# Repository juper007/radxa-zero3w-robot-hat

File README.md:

# Radxa ZERO 3W Robot HAT

A **strict single-board port** of Pollen Robotics' Apache-2.0 [`elec_RPI_Robot_HAT`](https://github.com/pollen-robotics/elec_RPI_Robot_HAT) for the Radxa ZERO 3W.

## Scope

The active design preserves the upstream product architecture:

- one 65 × 31 mm four-layer HAT PCB;
- the upstream 5–28 V power-input and 5 V conversion concept;
- on-board Dynamixel TTL/RS-485 circuitry and connectors;
- on-board BMI088 IMU, audio codec, MEMS microphone, speaker and expansion connectors;
- the original routed PCB as the layout baseline.

There is **no power daughterboard** in this branch. The earlier split-power redesign is preserved separately on `archive/v027-split-hat` at commit `2f2afd8`.

## Radxa-specific changes

Only host-facing compatibility changes are active:

| Physical pins | Upstream use | Radxa ZERO 3W use |
|---|---|---|
| 3 / 5 | Raspberry Pi I2C1 (`GPIO2/3`) | RK3566 `I2C3_SDA/SCL_M0` |
| 8 / 10 | Raspberry Pi UART (`GPIO14/15`) | RK3566 `UART2_TX/RX_M0` |
| 12 / 35 / 38 / 40 | Raspberry Pi PCM/I2S | RK3566 `I2S3_SCLK/LRCK/SDI/SDO_M0` |
| 2 / 4 | 5 V host rail | Radxa 5 V input pins |
| 1 / 17 | 3.3 V | Radxa 3.3 V rail |

The schematic and PCB net names identify these Radxa functions instead of Raspberry Pi BCM names. The physical routes are retained because the required interfaces occupy the same header pins.

The Raspberry Pi HAT EEPROM is retained as upstream DNP. All four upstream Qwiic connectors are populated for functional parity. J5 remains on hardware I2C3 M0 pins 3/5 with the codec and IMU. J6/J7/J8 retain the upstream routed GPIO pairs and are exposed as independent open-drain `i2c-gpio` buses by [`software/overlays/radxa-zero3w-robot-hat-qwiic.dts`](software/overlays/radxa-zero3w-robot-hat-qwiic.dts). Their original 0 Ω links and 10 kΩ pull-ups are populated.

## Software requirement

Using hardware I2C3 M0 on pins 3/5 requires the Radxa device-tree configuration to select `i2c3m0_xfer`. On vendor device trees this can conflict with the FUSB302 USB-C PD controller on I2C3 M1; the software overlay and resulting USB-C behavior must be reviewed before release. The Qwiic parity overlay adds J6/J7/J8 as aliases `i2c10`, `i2c11` and `i2c12`; the intended OS image must enable `CONFIG_I2C_GPIO`, leave those six GPIOs unclaimed, and pass runtime enumeration and transfer tests.

## Source and validation

- Upstream source revision: `23eab11927f95ceca0dfa35bf182caeb7db39ea0`
- KiCad sources: [`hardware/kicad/`](hardware/kicad/)
- Change matrix: [`docs/09_STRICT_PORT_CHANGE_MATRIX.md`](docs/09_STRICT_PORT_CHANGE_MATRIX.md)
- Current status: [`docs/PROJECT_STATUS.md`](docs/PROJECT_STATUS.md)
- Power review: [`docs/10_POWER_INTEGRITY_REVIEW.md`](docs/10_POWER_INTEGRITY_REVIEW.md)
- Mechanical/RF review: [`docs/11_RADXA_MECHANICAL_REVIEW.md`](docs/11_RADXA_MECHANICAL_REVIEW.md)
- Validation evidence: [`validation/strict_port/`](validation/strict_port/)

The routed board is **not yet approved for fabrication**. KiCad 10.0.6 CI regenerates reports from both the port and pinned upstream commit and locks rule policy, J4, the C45/U9 power region and the filled zone. Current DRC has zero findings and zero unconnected items after project-local footprint vendoring. Remaining gates include J4 supplier/prototype signoff, C45 physical gap, the 2 A load/thermal envelope, single-source backfeed testing, external-antenna/OTA policy, cable access and final manufacturing-package review.

## License and attribution

The active KiCad design is a modified derivative of Pollen Robotics' `elec_RPI_Robot_HAT`, licensed under Apache License 2.0. Upstream authorship and the exact source revision are preserved in the project documentation.

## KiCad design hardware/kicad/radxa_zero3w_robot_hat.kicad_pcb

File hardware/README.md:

# Hardware

## Active strict-port design

The active KiCad project is a single-board derivative of Pollen Robotics' `elec_RPI_Robot_HAT` at upstream commit `23eab11927f95ceca0dfa35bf182caeb7db39ea0`.

- `kicad/radxa_zero3w_robot_hat.kicad_pro` — project
- `kicad/radxa_zero3w_robot_hat.kicad_sch` — top-level schematic
- `kicad/radxa_zero3w_robot_hat.kicad_pcb` — routed 65.00 × 30.90 mm Edge.Cuts-centerline PCB (approximately 65 × 31 mm)
- Fixed order stackup — 4-layer FR-4, 1.0 mm, 70/35/35/70 µm copper, ENIG
- `kicad/main.kicad_sch` — 40-pin header and board integration
- `kicad/power.kicad_sch` / `pwr_supply_charge.kicad_sch` — upstream single-board power concept with local C45 input-bypass correction
- `kicad/dynamixel.kicad_sch` — upstream TTL/RS-485 interface and connectors
- `kicad/sensors.kicad_sch` — upstream BMI088 and Qwiic circuitry
- `kicad/audio.kicad_sch` — upstream codec, microphone and speaker circuitry

There is no active power daughterboard. The earlier split design is isolated on `archive/v027-split-hat`.

## Applied host changes

Critical nets retain their upstream physical header pins and routed copper while using Radxa names:

- pins 3/5 — `I2C3_SDA_M0` / `I2C3_SCL_M0`
- pins 8/10 — `UART2_TX_M0` / `UART2_RX_M0`
- pins 12/35/38/40 — `I2S3_SCLK_M0` / `I2S3_LRCK_M0` / `I2S3_SDI_M0` / `I2S3_SDO_M0`

U4 remains DNP. J5/J6/J7/J8 are all populated to preserve the upstream Qwiic expansion function. J6 uses R18/R19 0 Ω links plus R20/R21 10 kΩ pull-ups; J7 uses R34/R35 pull-ups; J8 uses R38/R39 pull-ups. The preserved J6/J7/J8 GPIO pairs are configured as three independent software I2C buses by the Radxa overlay under `../software/overlays/`.

## Validation

See `../validation/strict_port/` and `kicad/check_strict_port.py`.

The adapted design has 48 ERC warnings: eight upstream footprint-link findings are resolved by the vendored project-local libraries, and one exact C45 `lib_symbol_mismatch` remains approved pending symbol-library cleanup. It retains 110 remaining `Datasheet` field parity warnings; one inherited J4 field mismatch was resolved by correcting the manufacturing identity. All 49 upstream DRC findings are resolved, so current native DRC contains zero findings and zero unconnected items. C45 adds 10 µF / 50 V X7R input bypass; C21/C22 metadata correctly states 22 µF / 10 V, and the local U9/D1/C22 routing plus filled zone are hash-locked. The current board has 128 footprints and 1,013 track/via items. Twelve exact footprint definitions and `fp-lib-table` are hash-locked by `vendored_footprints_manifest.json`. J4 vendor/prototype approval, C45's ≥4.0 mm PCB gap and ≥0.5 mm residual-clearance gate, the 2 A EVT load/thermal envelope, antenna policy and single-source power rule remain fabrication gates.

## Upstream libraries

The 12 footprint definitions needed for `Library_Pollen`, `LCSC_parts_lib` and the board-used `Package_TO_SOT_SMD` subset are vendored under `kicad/*.pretty/` and mapped by `kicad/fp-lib-table`. `kicad/vendored_footprints_manifest.json` pins the exact file inventory and hashes. This removes all native DRC footprint-library findings without changing the embedded PCB, placement, pads, nets or routing. Some 3D-model paths still retain upstream names for traceability and may require later model vendoring for complete assembly rendering.

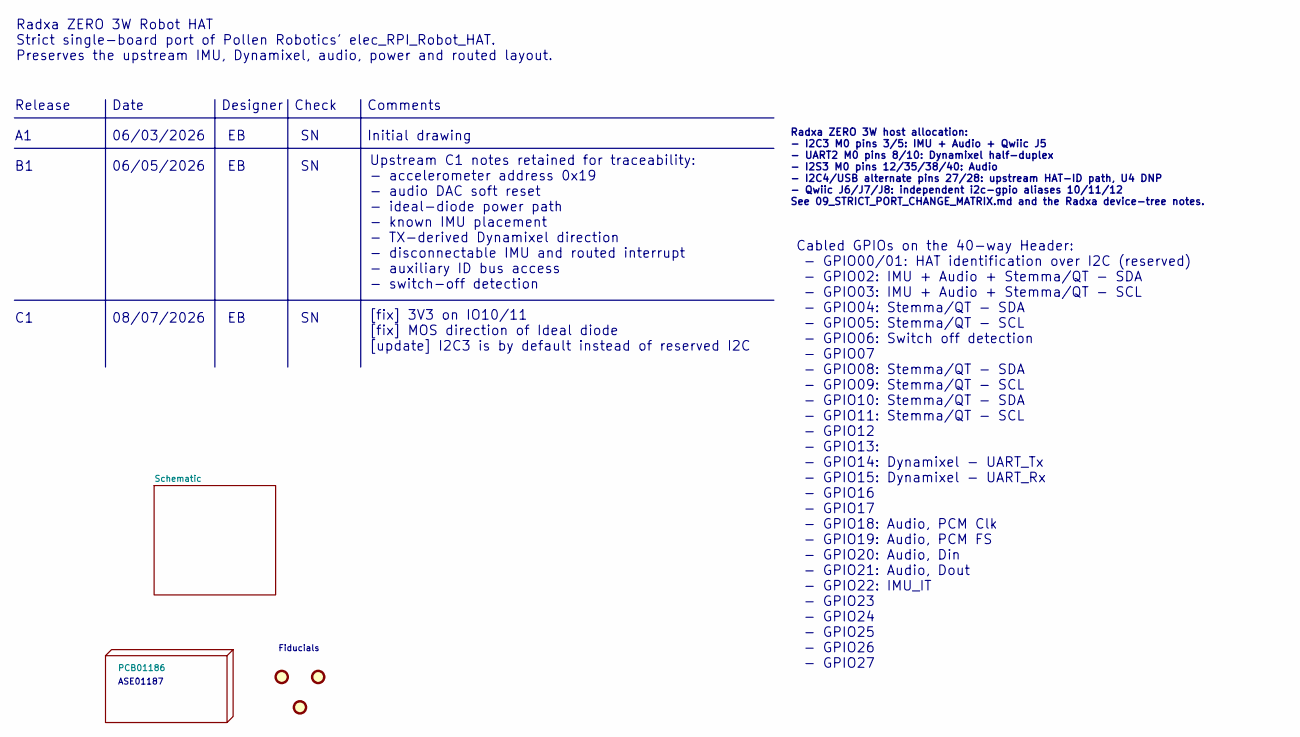
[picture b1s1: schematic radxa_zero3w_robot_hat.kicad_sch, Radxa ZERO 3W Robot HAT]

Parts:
FID1, FID2, FID3: DNP Fiducial; Fiducial_1mm_Mask2mm
H1: PCB01186

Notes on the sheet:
Upstream C1 notes retained for traceability: - accelerometer address 0x19 - audio DAC soft reset - ideal-diode power path - known IMU placement - TX-derived Dynamixel direction - disconnectable IMU and routed interrupt - auxiliary ID bus access - switch-off detection
Date
[fix] 3V3 on IO10/11 [fix] MOS direction of Ideal diode [update] I2C3 is by default instead of reserved I2C
Check
Release
Fiducials
Radxa ZERO 3W host allocation: - I2C3 M0 pins 3/5: IMU + Audio + Qwiic J5 - UART2 M0 pins 8/10: Dynamixel half-duplex - I2S3 M0 pins 12/35/38/40: Audio - I2C4/USB alternate pins 27/28: upstream HAT-ID path, U4 DNP - Qwiic J6/J7/J8: independent i2c-gpio aliases 10/11/12 See 09_STRICT_PORT_CHANGE_MAT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
08/07/2026
ASE01187
06/05/2026
Initial drawing
Radxa ZERO 3W Robot HAT Strict single-board port of Pollen Robotics' elec_RPI_Robot_HAT. Preserves the upstream IMU, Dynamixel, audio, power and routed layout.
Designer
Cabled GPIOs on the 40-way Header: - GPIO00/01: HAT identification over I2C (reserved) - GPIO02: IMU + Audio + Stemma/QT - SDA - GPIO03: IMU + Audio + Stemma/QT - SCL - GPIO04: Stemma/QT - SDA - GPIO05: Stemma/QT - SCL - GPIO06: Switch off detection - GPIO07 - GPIO08: Stemma/QT - SDA - GPIO09: Stem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
Comments
06/03/2026

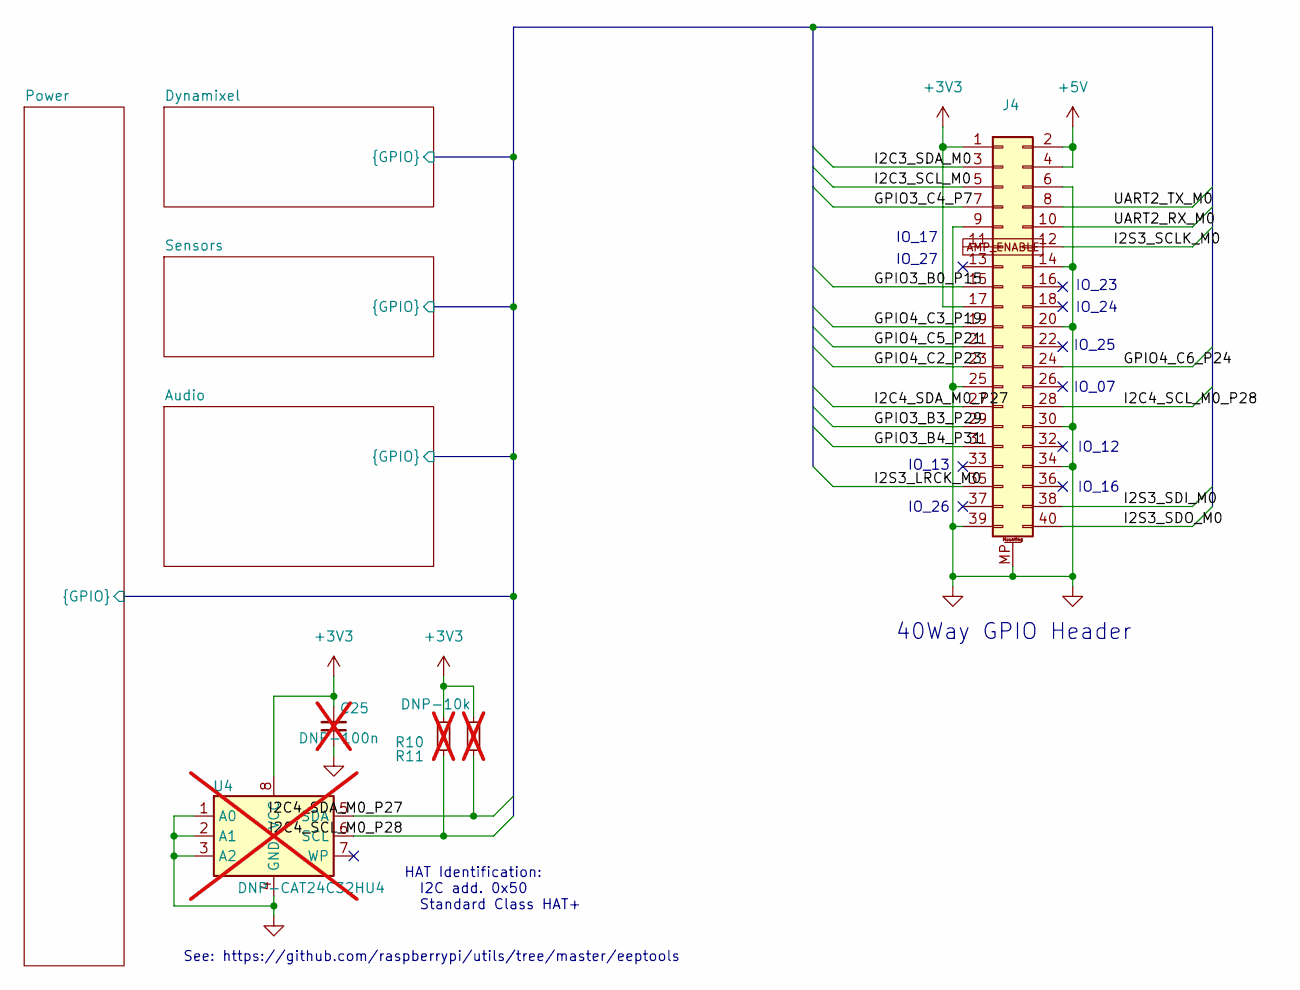
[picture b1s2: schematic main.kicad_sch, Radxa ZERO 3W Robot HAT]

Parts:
C25: DNP-100n; C_0402_1005Metric; not fitted
J4: Radxa ZERO 3W 2x20 HAT Header; PinHeader_2x20_P2.54mm_Vertical_with_rasp_HAT_zero_SMD_conn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; Part Description 2x20 2.54 mm surface-mount bottom-entry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
R10, R11: DNP-10k; R_0402_1005Metric; not fitted
U4: DNP-CAT24C32HU4; TDFN-8_L3.0-W2.0-P0.50-BL-EP; not fitted

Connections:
+3V3: C25.2, J4.1, J4.17, R10.1, R11.1, U4.8 (VCC); also elsewhere on the board
+5V: J4.2, J4.4; also elsewhere on the board
/Schematic/Audio/GPIO3_B0_P15: J4.15; also elsewhere on the board
/Schematic/Audio/GPIO3_B3_P29: J4.29; also elsewhere on the board
/Schematic/Audio/GPIO3_B4_P31: J4.31; also elsewhere on the board
/Schematic/Audio/GPIO3_C4_P7: J4.7; also elsewhere on the board
/Schematic/Audio/GPIO4_C2_P23: J4.23; also elsewhere on the board
/Schematic/Audio/GPIO4_C3_P19: J4.19; also elsewhere on the board
/Schematic/Audio/GPIO4_C5_P21: J4.21; also elsewhere on the board
/Schematic/Audio/GPIO4_C6_P24: J4.24; also elsewhere on the board
/Schematic/Audio/I2C3_SCL_M0: J4.5; also elsewhere on the board
/Schematic/Audio/I2C3_SDA_M0: J4.3; also elsewhere on the board
/Schematic/Audio/I2C4_SCL_M0_P28: J4.28, R10.2, U4.6 (SCL); also elsewhere on the board
/Schematic/Audio/I2C4_SDA_M0_P27: J4.27, R11.2, U4.5 (SDA); also elsewhere on the board
/Schematic/Audio/I2S3_LRCK_M0: J4.35; also elsewhere on the board
/Schematic/Audio/I2S3_SCLK_M0: J4.12; also elsewhere on the board
/Schematic/Audio/I2S3_SDI_M0: J4.38; also elsewhere on the board
/Schematic/Audio/I2S3_SDO_M0: J4.40; also elsewhere on the board
/Schematic/Audio/UART2_RX_M0: J4.10; also elsewhere on the board
/Schematic/Audio/UART2_TX_M0: J4.8; also elsewhere on the board
AMP_ENABLE: J4.11; also elsewhere on the board
GND: C25.1, J4.6, J4.9, J4.14, J4.20, J4.25, J4.30, J4.34, J4.39, J4.MP (MountPin), U4.1 (A0), U4.2 (A1), U4.3 (A2), U4.4 (GND); also elsewhere on the board

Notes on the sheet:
IO_07
IO_23
40Way GPIO Header
IO_13
IO_24
HAT Identification: I2C add. 0x50 Standard Class HAT+
IO_25
IO_17
IO_12
See: https://github.com/raspberrypi/utils/tree/master/eeptools
IO_16
IO_26
IO_27

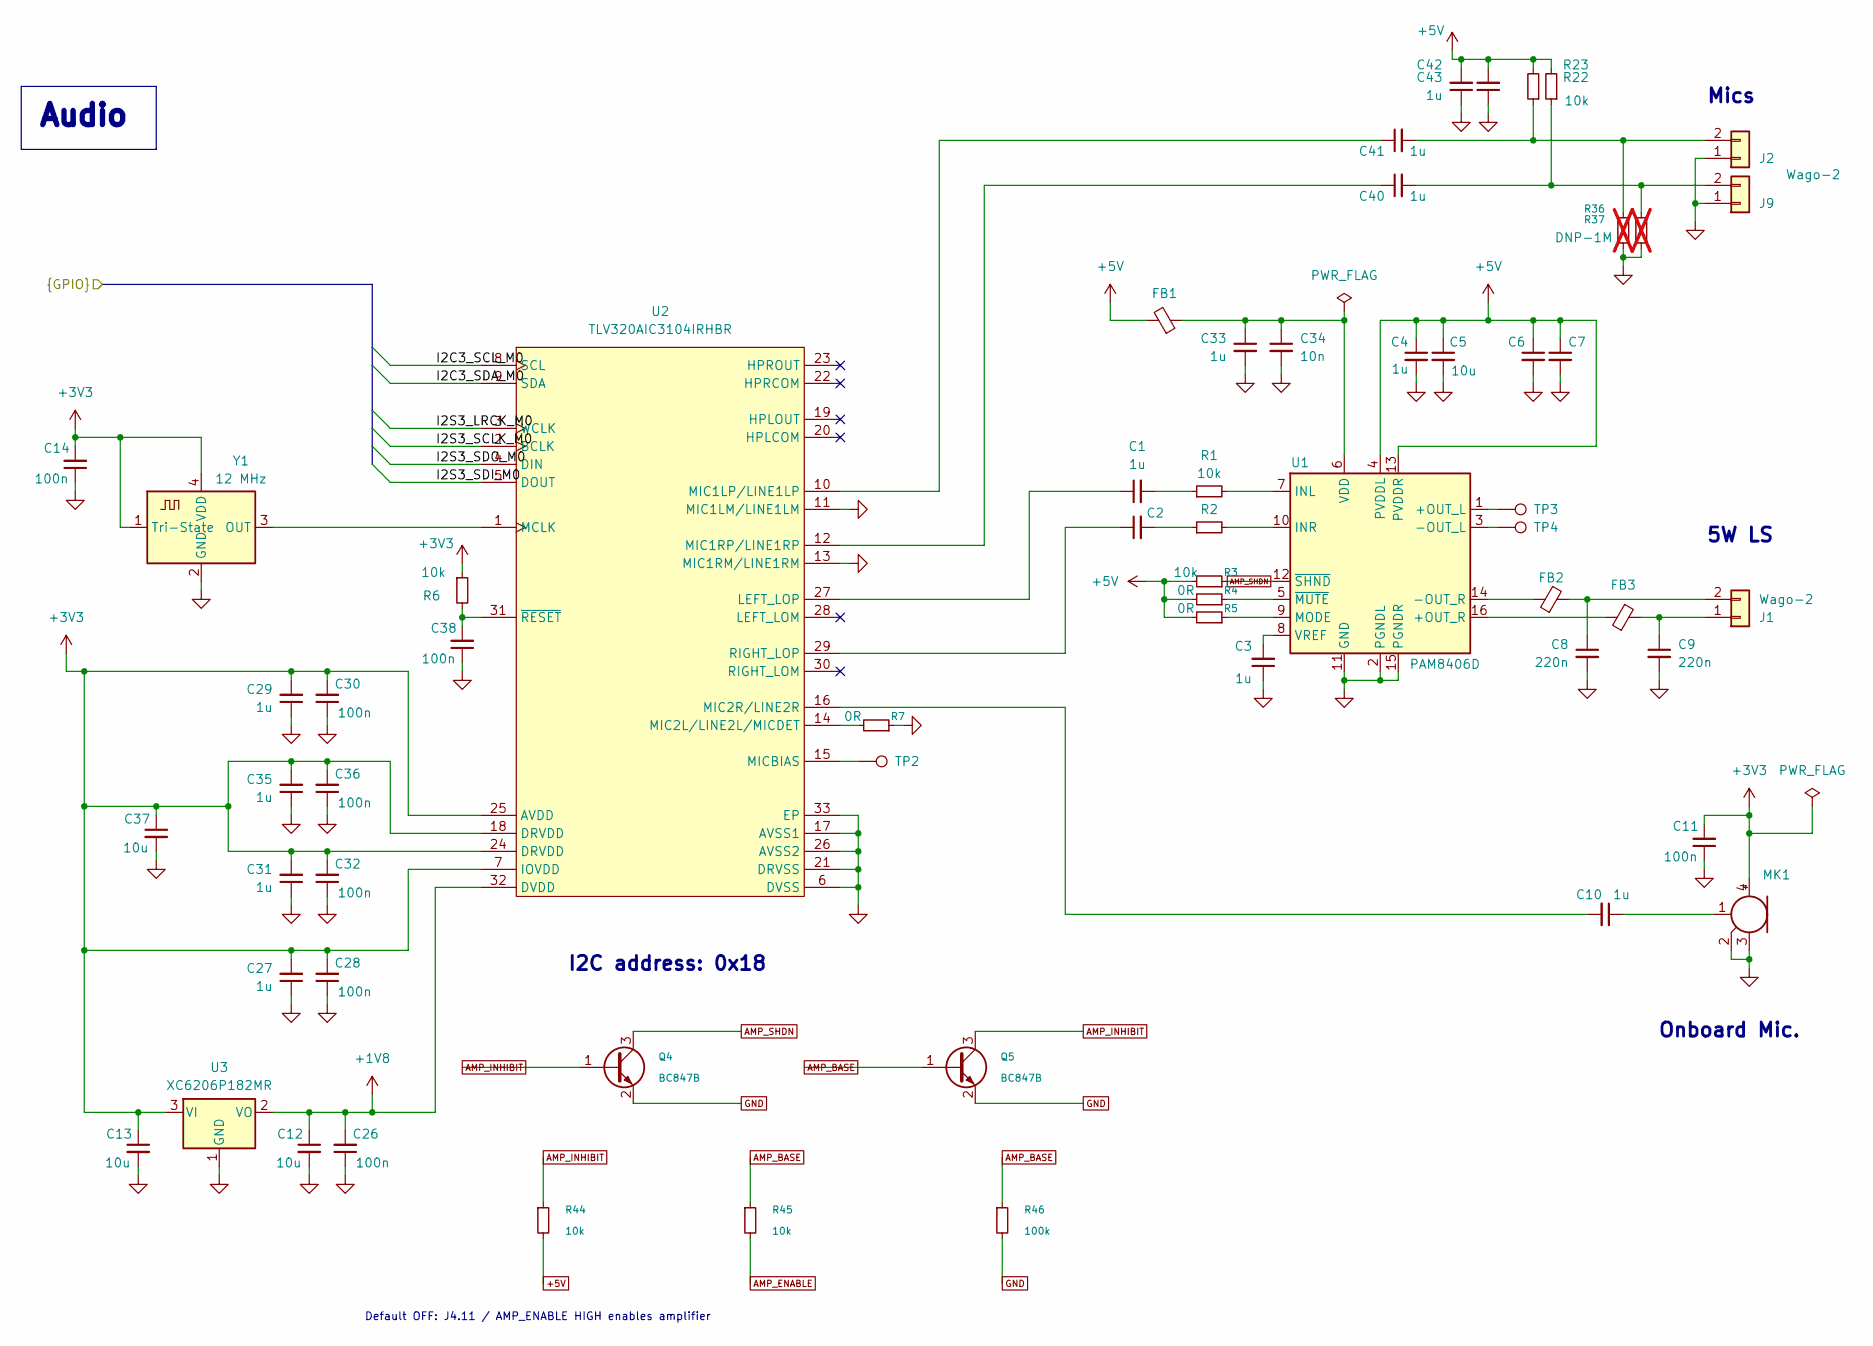
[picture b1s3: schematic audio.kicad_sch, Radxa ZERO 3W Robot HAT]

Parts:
C1, C2, C3, C4, C6, C10, C27, C29, C31, C33, C35, C40, C41, C42, C43: 1u; C_0402_1005Metric; LCSC Part C52923
C5, C7, C12, C13, C37: 10u; C_0603_1608Metric; LCSC Part C1691
C8, C9: 220n; C_0402_1005Metric; LCSC Part C71693
C11, C14, C26, C28, C30, C32, C36, C38: 100n; C_0402_1005Metric; LCSC Part C307331
C34: 10n; C_0402_1005Metric; LCSC Part C15195
FB1: 1.3A 600R@100MHz; L_0402_1005Metric; LCSC Part C76884
FB2, FB3: 2A - 120R@100MHz; L_0402_1005Metric; LCSC Part C88970
J1, J2, J9: Wago-2; Wago_2059-302_998-403; LCSC Part C2765060
MK1: Microphone_MEMS; MIC-SMD_4P-L2.8-W1.9-P1.84-TL; LCSC Part C7587901
Q4, Q5: BC847B; SOT-23; Manufacturer_Part_Number BC847B,215
R1, R2, R6, R22, R23: 10k; R_0402_1005Metric; LCSC Part C25744
R3, R44, R45: 10k; R_0402_1005Metric; Power Rating 0.063W; Tolerance 1%; Manufacturer_Part_Number RC0402FR-0710KL
R4, R5, R7: 0R; R_0402_1005Metric; LCSC Part C17168
R36, R37: DNP-1M; R_0402_1005Metric; LCSC Part C17168; not fitted
R46: 100k; R_0402_1005Metric; Power Rating 0.063W; Tolerance 1%; Manufacturer_Part_Number RC0402FR-07100KL
TP2, TP3, TP4: TestPoint; TestPoint_Loop_D2.50mm_Drill1.0mm_LowProfile
U1: PAM8406D; SOIC-16_3.9x9.9mm_P1.27mm; LCSC Part C86270
U2: TLV320AIC3104IRHBR; VQFN-32-1EP_5x5mm_P0.5mm_EP3.5x3.5mm; LCSC Part C181753
U3: XC6206P182MR; SOT-23-3; LCSC Part C347373
Y1: 12 MHz; Oscillator_SMD_Abracon_ASDMB-4Pin_2.5x2.0mm; LCSC Part C7425459

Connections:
+1V8: C12.1, C26.2, U2.32 (DVDD), U3.2 (VO)
+3V3: C11.2, C13.1, C14.2, C27.2, C28.2, C29.2, C30.2, C31.2, C32.2, C35.2, C36.2, C37.1, MK1.4 (+), R6.1, U2.7 (IOVDD), U2.18 (DRVDD), U2.24 (DRVDD), U2.25 (AVDD), U3.3 (VI), Y1.1 (Tri-State), Y1.4 (VDD); also elsewhere on the board
+5V: C4.1, C5.1, C6.1, C7.1, C42.2, C43.2, FB1.2, R3.2, R4.2, R5.2, R22.2, R23.2, R44.2, U1.4 (PVDDL), U1.13 (PVDDR); also elsewhere on the board
/Schematic/Audio/I2C3_SCL_M0: U2.8 (SCL); also elsewhere on the board
/Schematic/Audio/I2C3_SDA_M0: U2.9 (SDA); also elsewhere on the board
/Schematic/Audio/I2S3_LRCK_M0: U2.3 (WCLK); also elsewhere on the board
/Schematic/Audio/I2S3_SCLK_M0: U2.2 (BCLK); also elsewhere on the board
/Schematic/Audio/I2S3_SDI_M0: U2.5 (DOUT); also elsewhere on the board
/Schematic/Audio/I2S3_SDO_M0: U2.4 (DIN); also elsewhere on the board
AMP_BASE: Q5.1 (B), R45.1, R46.1
AMP_ENABLE: R45.2; also elsewhere on the board
AMP_INHIBIT: Q4.1 (B), Q5.3 (C), R44.1
AMP_SHDN: Q4.3 (C), R3.1, U1.12 (~SHND)
GND: C3.1, C4.2, C5.2, C6.2, C7.2, C8.2, C9.2, C11.1, C12.2, C13.2, C14.1, C26.1, C27.1, C28.1, C29.1, C30.1, C31.1, C32.1, C33.2, C34.2, C35.1, C36.1, C37.2, C38.1, C42.1, C43.1, J2.1, J9.1, MK1.2 (-), MK1.3 (-), Q4.2 (E), Q5.2 (E), R7.1, R36.1, R37.1, R46.2, U1.2 (PGNDL), U1.11 (GND), U1.15 (PGNDR), U2.6 (DVSS), U2.11 (MIC1LM/LINE1LM), U2.13 (MIC1RM/LINE1RM), U2.17 (AVSS1), U2.21 (DRVSS), U2.26 (AVSS2), U2.33 (EP), U3.1 (GND), Y1.2 (GND); also elsewhere on the board
unnamed: C1.2, R1.1
unnamed: C2.2, R2.1
unnamed: C10.1, MK1.1 (-)
unnamed: C9.1, FB3.2, J1.1
unnamed: C8.1, FB2.2, J1.2
unnamed: C41.2, J2.2, R22.1, R36.2
unnamed: C40.2, J9.2, R23.1, R37.2
unnamed: TP3.1, U1.1 (+OUT_L)
unnamed: FB3.1, U1.16 (+OUT_R)
unnamed: TP4.1, U1.3 (-OUT_L)
unnamed: FB2.1, U1.14 (-OUT_R)
unnamed: R1.2, U1.7 (INL)
unnamed: R2.2, U1.10 (INR)
unnamed: R5.1, U1.9 (MODE)
unnamed: C33.1, C34.1, FB1.1, U1.6 (VDD)
unnamed: C3.2, U1.8 (VREF)
unnamed: R4.1, U1.5 (~MUTE)
unnamed: C1.1, U2.27 (LEFT_LOP)
unnamed: U2.1 (MCLK), Y1.3 (OUT)
unnamed: C41.1, U2.10 (MIC1LP/LINE1LP)
unnamed: C40.1, U2.12 (MIC1RP/LINE1RP)
unnamed: R7.2, U2.14 (MIC2L/LINE2L/MICDET)
unnamed: C10.2, U2.16 (MIC2R/LINE2R)
unnamed: TP2.1, U2.15 (MICBIAS)
unnamed: C2.1, U2.29 (RIGHT_LOP)
unnamed: C38.2, R6.2, U2.31 (~RESET)

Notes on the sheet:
Onboard Mic.
5W LS
Mics
I2C address: 0x18
Audio
Default OFF: J4.11 / AMP_ENABLE HIGH enables amplifier

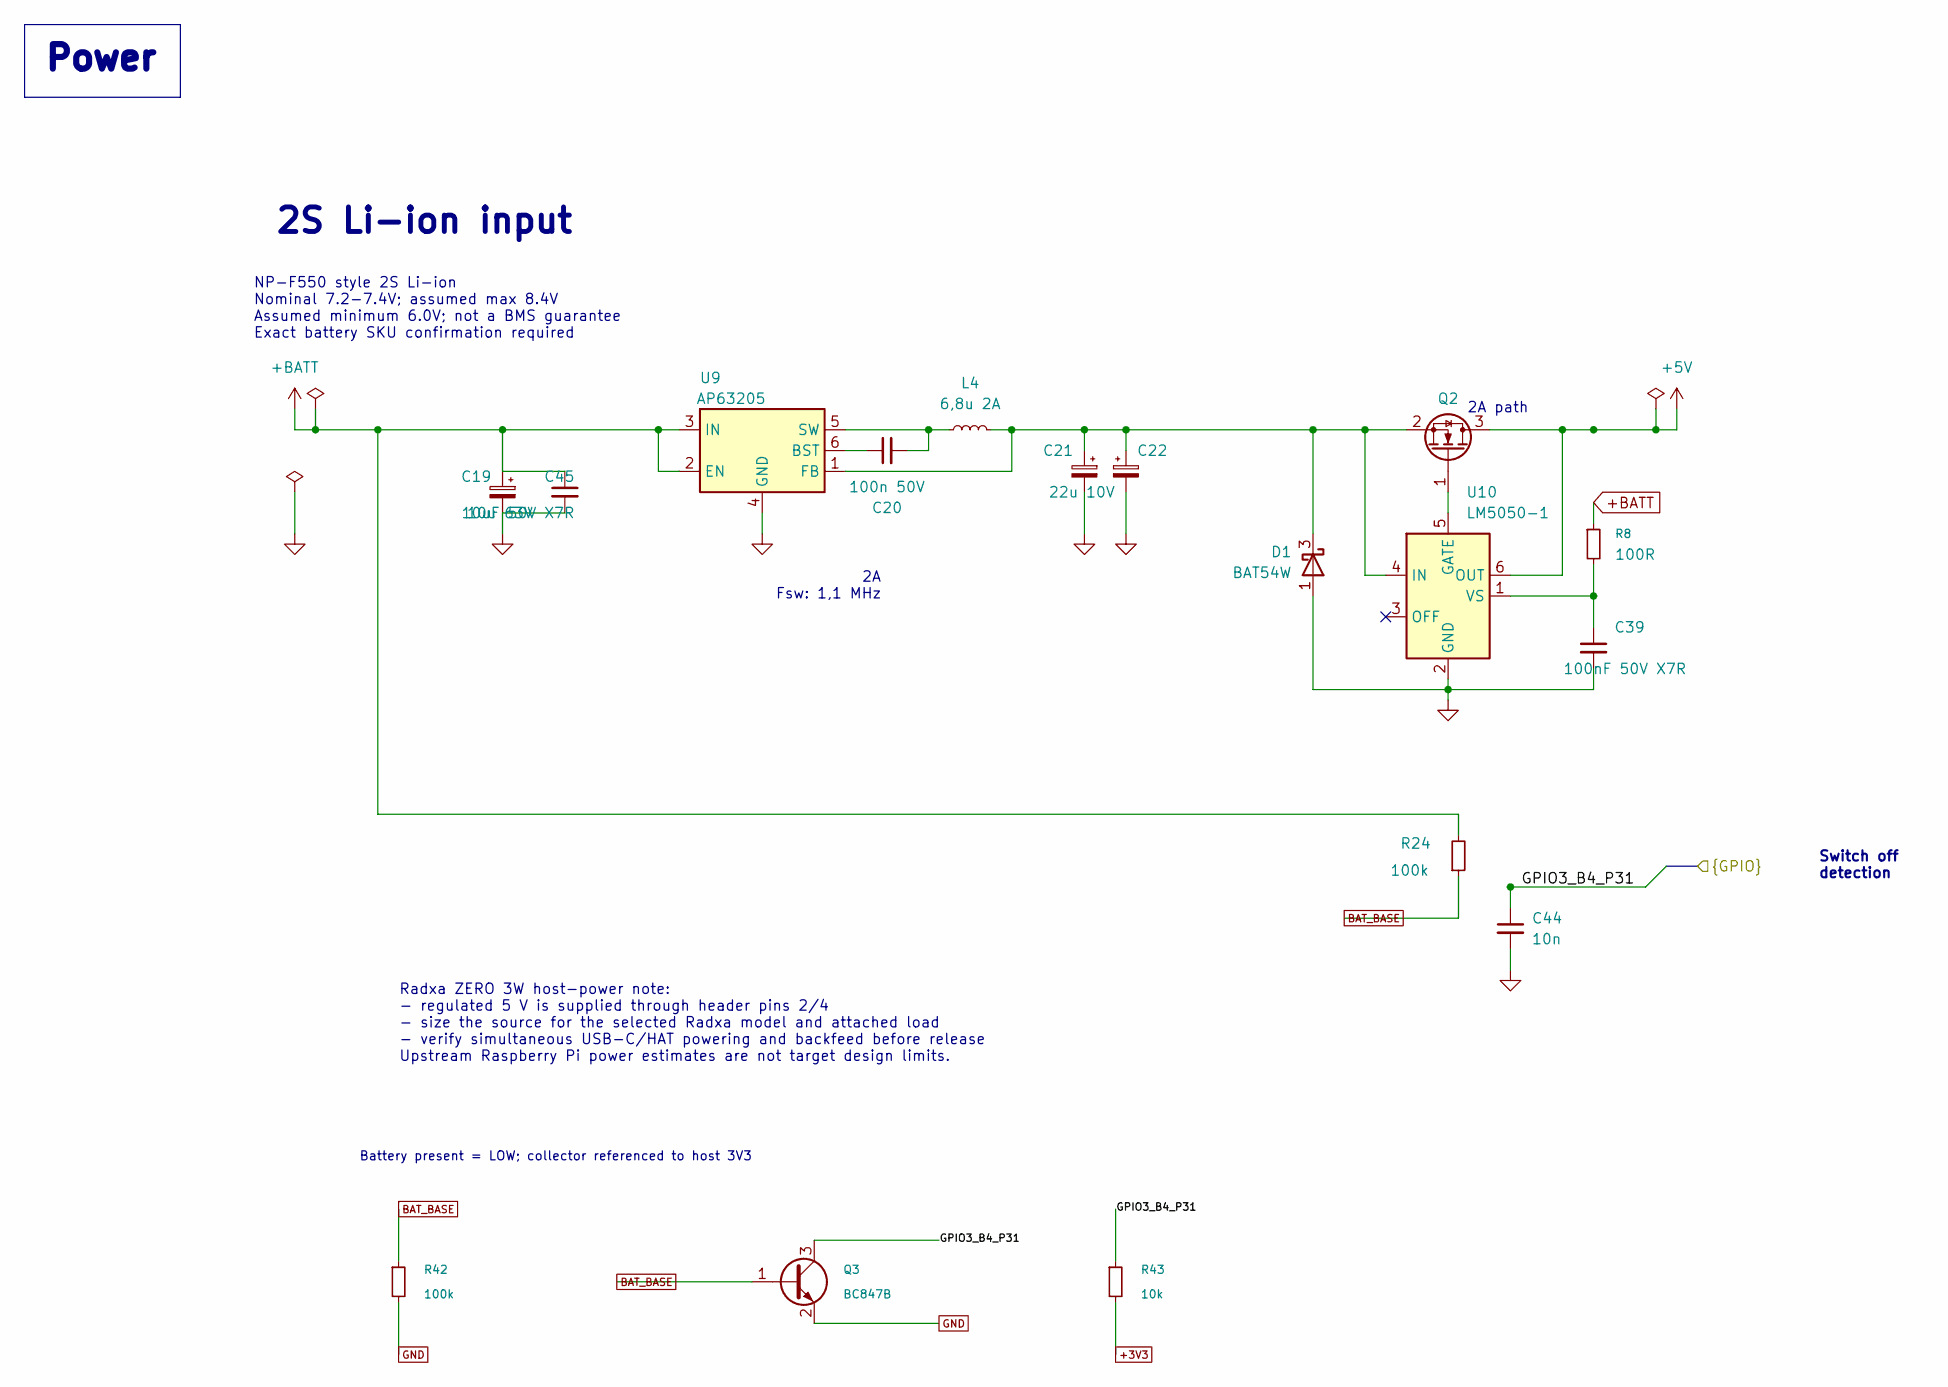
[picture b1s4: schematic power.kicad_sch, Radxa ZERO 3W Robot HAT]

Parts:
C19: 10u 63V; CP_Elec_6.3x7.7; LCSC Part C72488
C20: 100n 50V; C_0402_1005Metric; LCSC Part C307331
C21, C22: 22u 10V; C_0603_1608Metric; LCSC Part C84419
C39: 100nF 50V X7R; C_0402_1005Metric; Tolerance 10%; Voltage Rating 50V; Manufacturer_Part_Number CL05B104KB5NNNC
C44: 10n; C_0402_1005Metric; LCSC Part C15195
C45: 10uF 50V X7R; C_1210_3225Metric; Voltage Rating 50V; LCSC Part C77102
D1: BAT54W; SOT-323_SC-70; LCSC Part C78606
L4: 6,8u 2A; L_Bourns_SRN6045TA; LCSC Part C57254
Q2: DMN3023L-7; DMN3023L_SOT23_Diodes; Manufacturer_Part_Number DMN3023L-7; LCSC Part C443825
Q3: BC847B; SOT-23; Manufacturer_Part_Number BC847B,215
R8: 100R; R_0402_1005Metric; LCSC Part C2906860
R24, R42: 100k; R_0402_1005Metric; Power Rating 0.063W; Tolerance 1%; Manufacturer_Part_Number RC0402FR-07100KL
R43: 10k; R_0402_1005Metric; Power Rating 0.063W; Tolerance 1%; Manufacturer_Part_Number RC0402FR-0710KL
U9: AP63205; TSOT-23-6; LCSC Part C2071056
U10: LM5050-1; TSOT-23-6; LCSC Part C473393

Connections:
+3V3: R43.2; also elsewhere on the board
+5V: Q2.3 (D), U10.6 (OUT); also elsewhere on the board
+BATT: C19.1, C45.1, R8.1, R24.2, U9.2 (EN), U9.3 (IN); also elsewhere on the board
/Schematic/Audio/GPIO3_B4_P31: C44.1, Q3.3 (C), R43.1; also elsewhere on the board
BAT_BASE: Q3.1 (B), R24.1, R42.1
GND: C19.2, C21.2, C22.2, C39.2, C44.2, C45.2, D1.1 (A), Q3.2 (E), R42.2, U9.4 (GND), U10.2 (GND); also elsewhere on the board
unnamed: C21.1, C22.1, D1.3 (K), L4.1, Q2.2 (S), U9.1 (FB), U10.4 (IN)
unnamed: Q2.1 (G), U10.5 (GATE)
unnamed: C20.1, U9.6 (BST)
unnamed: C20.2, L4.2, U9.5 (SW)
unnamed: C39.1, R8.2, U10.1 (VS)

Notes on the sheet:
Switch off detection
2A path
2S Li-ion input
Radxa ZERO 3W host-power note: - regulated 5 V is supplied through header pins 2/4 - size the source for the selected Radxa model and attached load - verify simultaneous USB-C/HAT powering and backfeed before release Upstream Raspberry Pi power estimates are not target design limits.
NP-F550 style 2S Li-ion Nominal 7.2-7.4V; assumed max 8.4V Assumed minimum 6.0V; not a BMS guarantee Exact battery SKU confirmation required
2A Fsw: 1,1 MHz
Power
Battery present = LOW; collector referenced to host 3V3

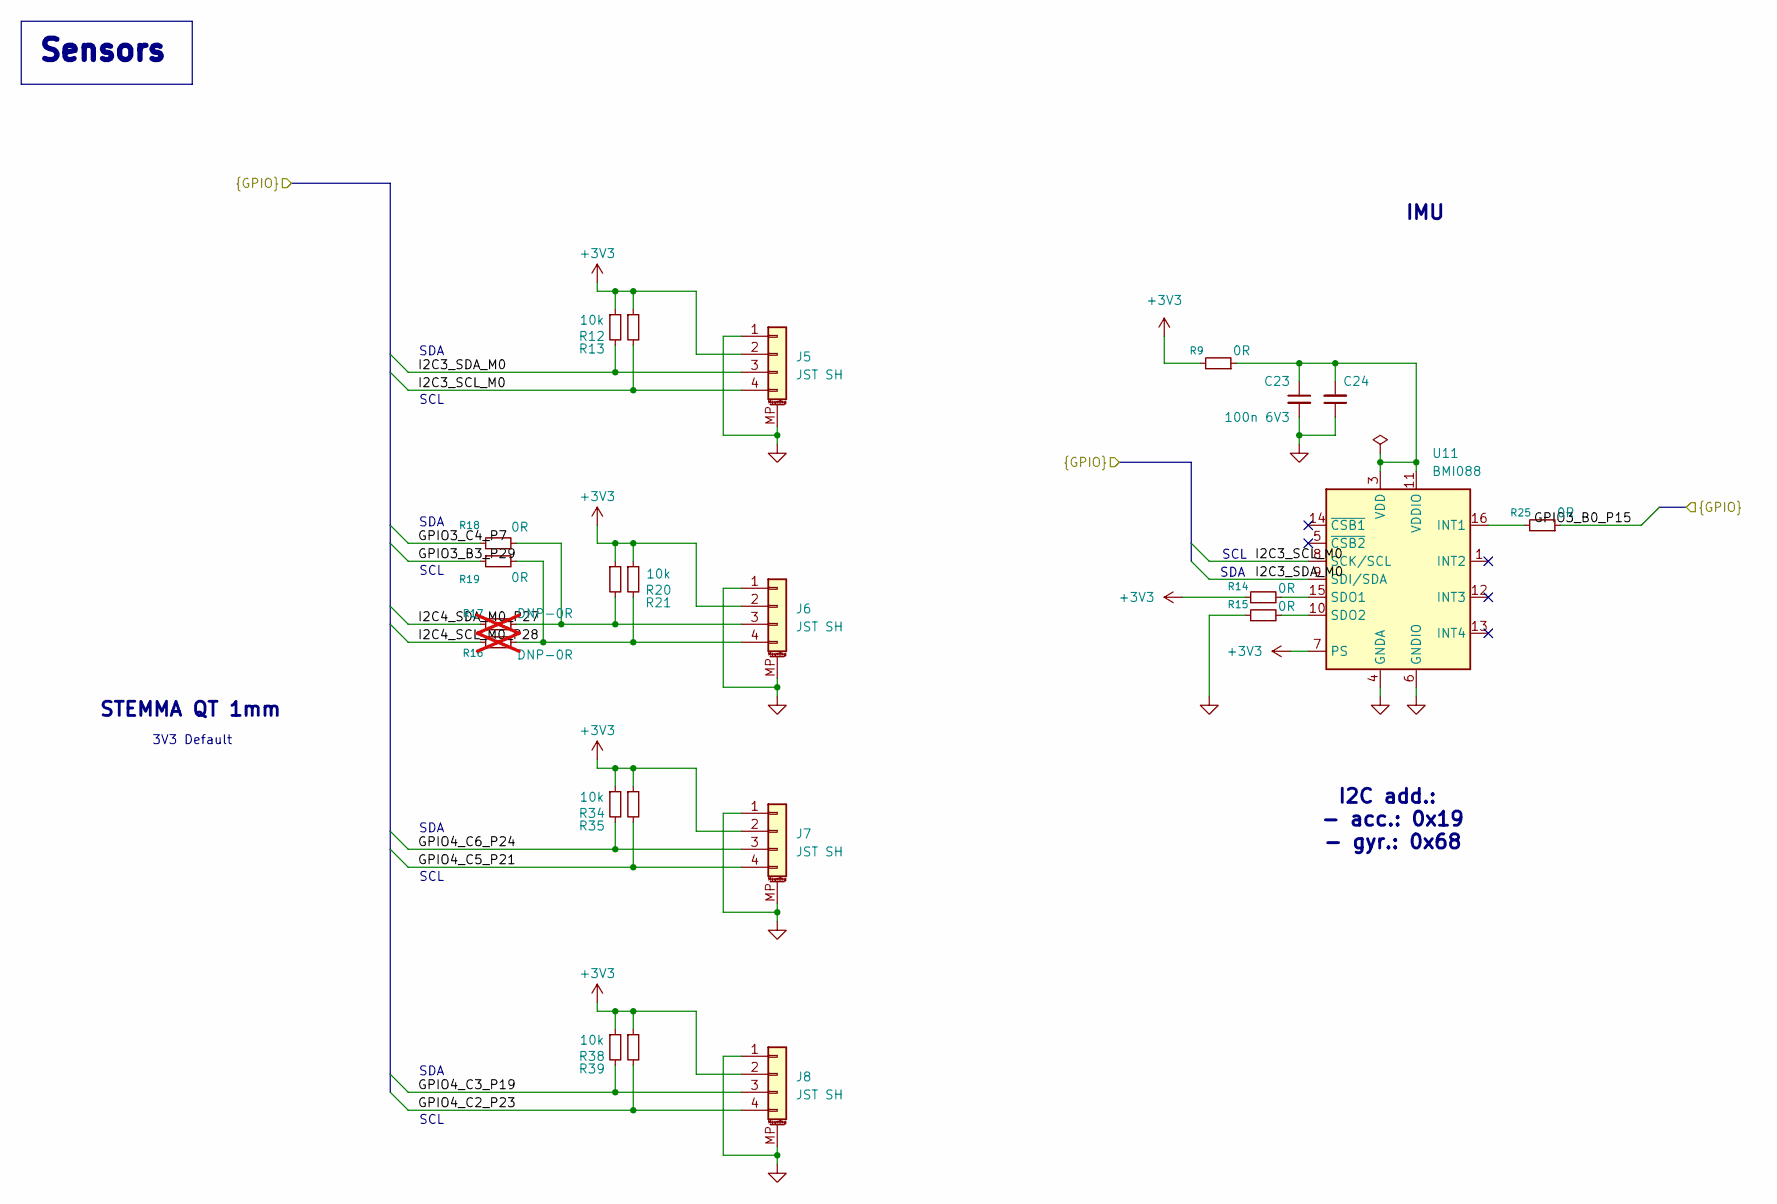
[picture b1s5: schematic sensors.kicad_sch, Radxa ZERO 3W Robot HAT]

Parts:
C23, C24: 100n 6V3; C_0402_1005Metric; LCSC Part C1525
J5, J6, J7, J8: JST SH; JST_SH_BM04B-SRSS-TB_1x04-1MP_P1.00mm_Vertical; LCSC Part C160390
R9, R14, R15, R18, R19, R25: 0R; R_0402_1005Metric; LCSC Part C17168
R12, R13, R20, R21, R34, R35, R38, R39: 10k; R_0402_1005Metric; LCSC Part C25744
R16, R17: DNP-0R; R_0402_1005Metric; not fitted
U11: BMI088; Bosch_LGA-16_4.5x3mm_P0.5mm_LayoutBorder7x1y_ClockwisePinNu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; LCSC Part C194919

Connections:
+3V3: J5.2, J6.2, J7.2, J8.2, R9.2, R12.1, R13.1, R14.1, R20.1, R21.1, R34.1, R35.1, R38.1, R39.1, U11.7 (PS); also elsewhere on the board
/Schematic/Audio/GPIO3_B0_P15: R25.1; also elsewhere on the board
/Schematic/Audio/GPIO3_B3_P29: R19.1; also elsewhere on the board
/Schematic/Audio/GPIO3_C4_P7: R18.1; also elsewhere on the board
/Schematic/Audio/GPIO4_C2_P23: J8.4, R39.2; also elsewhere on the board
/Schematic/Audio/GPIO4_C3_P19: J8.3, R38.2; also elsewhere on the board
/Schematic/Audio/GPIO4_C5_P21: J7.4, R35.2; also elsewhere on the board
/Schematic/Audio/GPIO4_C6_P24: J7.3, R34.2; also elsewhere on the board
/Schematic/Audio/I2C3_SCL_M0: J5.4, R13.2, U11.8 (SCK/SCL); also elsewhere on the board
/Schematic/Audio/I2C3_SDA_M0: J5.3, R12.2, U11.9 (SDI/SDA); also elsewhere on the board
/Schematic/Audio/I2C4_SCL_M0_P28: R16.1; also elsewhere on the board
/Schematic/Audio/I2C4_SDA_M0_P27: R17.1; also elsewhere on the board
GND: C23.2, C24.1, J5.1, J5.MP (MountPin), J6.1, J6.MP (MountPin), J7.1, J7.MP (MountPin), J8.1, J8.MP (MountPin), R15.1, U11.2 (GNDA), U11.4 (GNDA), U11.6 (GNDIO); also elsewhere on the board
unnamed: J6.3, R17.2, R18.2, R20.2
unnamed: J6.4, R16.2, R19.2, R21.2
unnamed: R25.2, U11.16 (INT1)
unnamed: R14.2, U11.15 (SDO1)
unnamed: R15.2, U11.10 (SDO2)
unnamed: C23.1, C24.2, R9.1, U11.3 (VDD), U11.11 (VDDIO)

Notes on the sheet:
SCL
SDA
I2C add.: - acc.: 0x19 - gyr.: 0x68
IMU
STEMMA QT 1mm
3V3 Default
Sensors

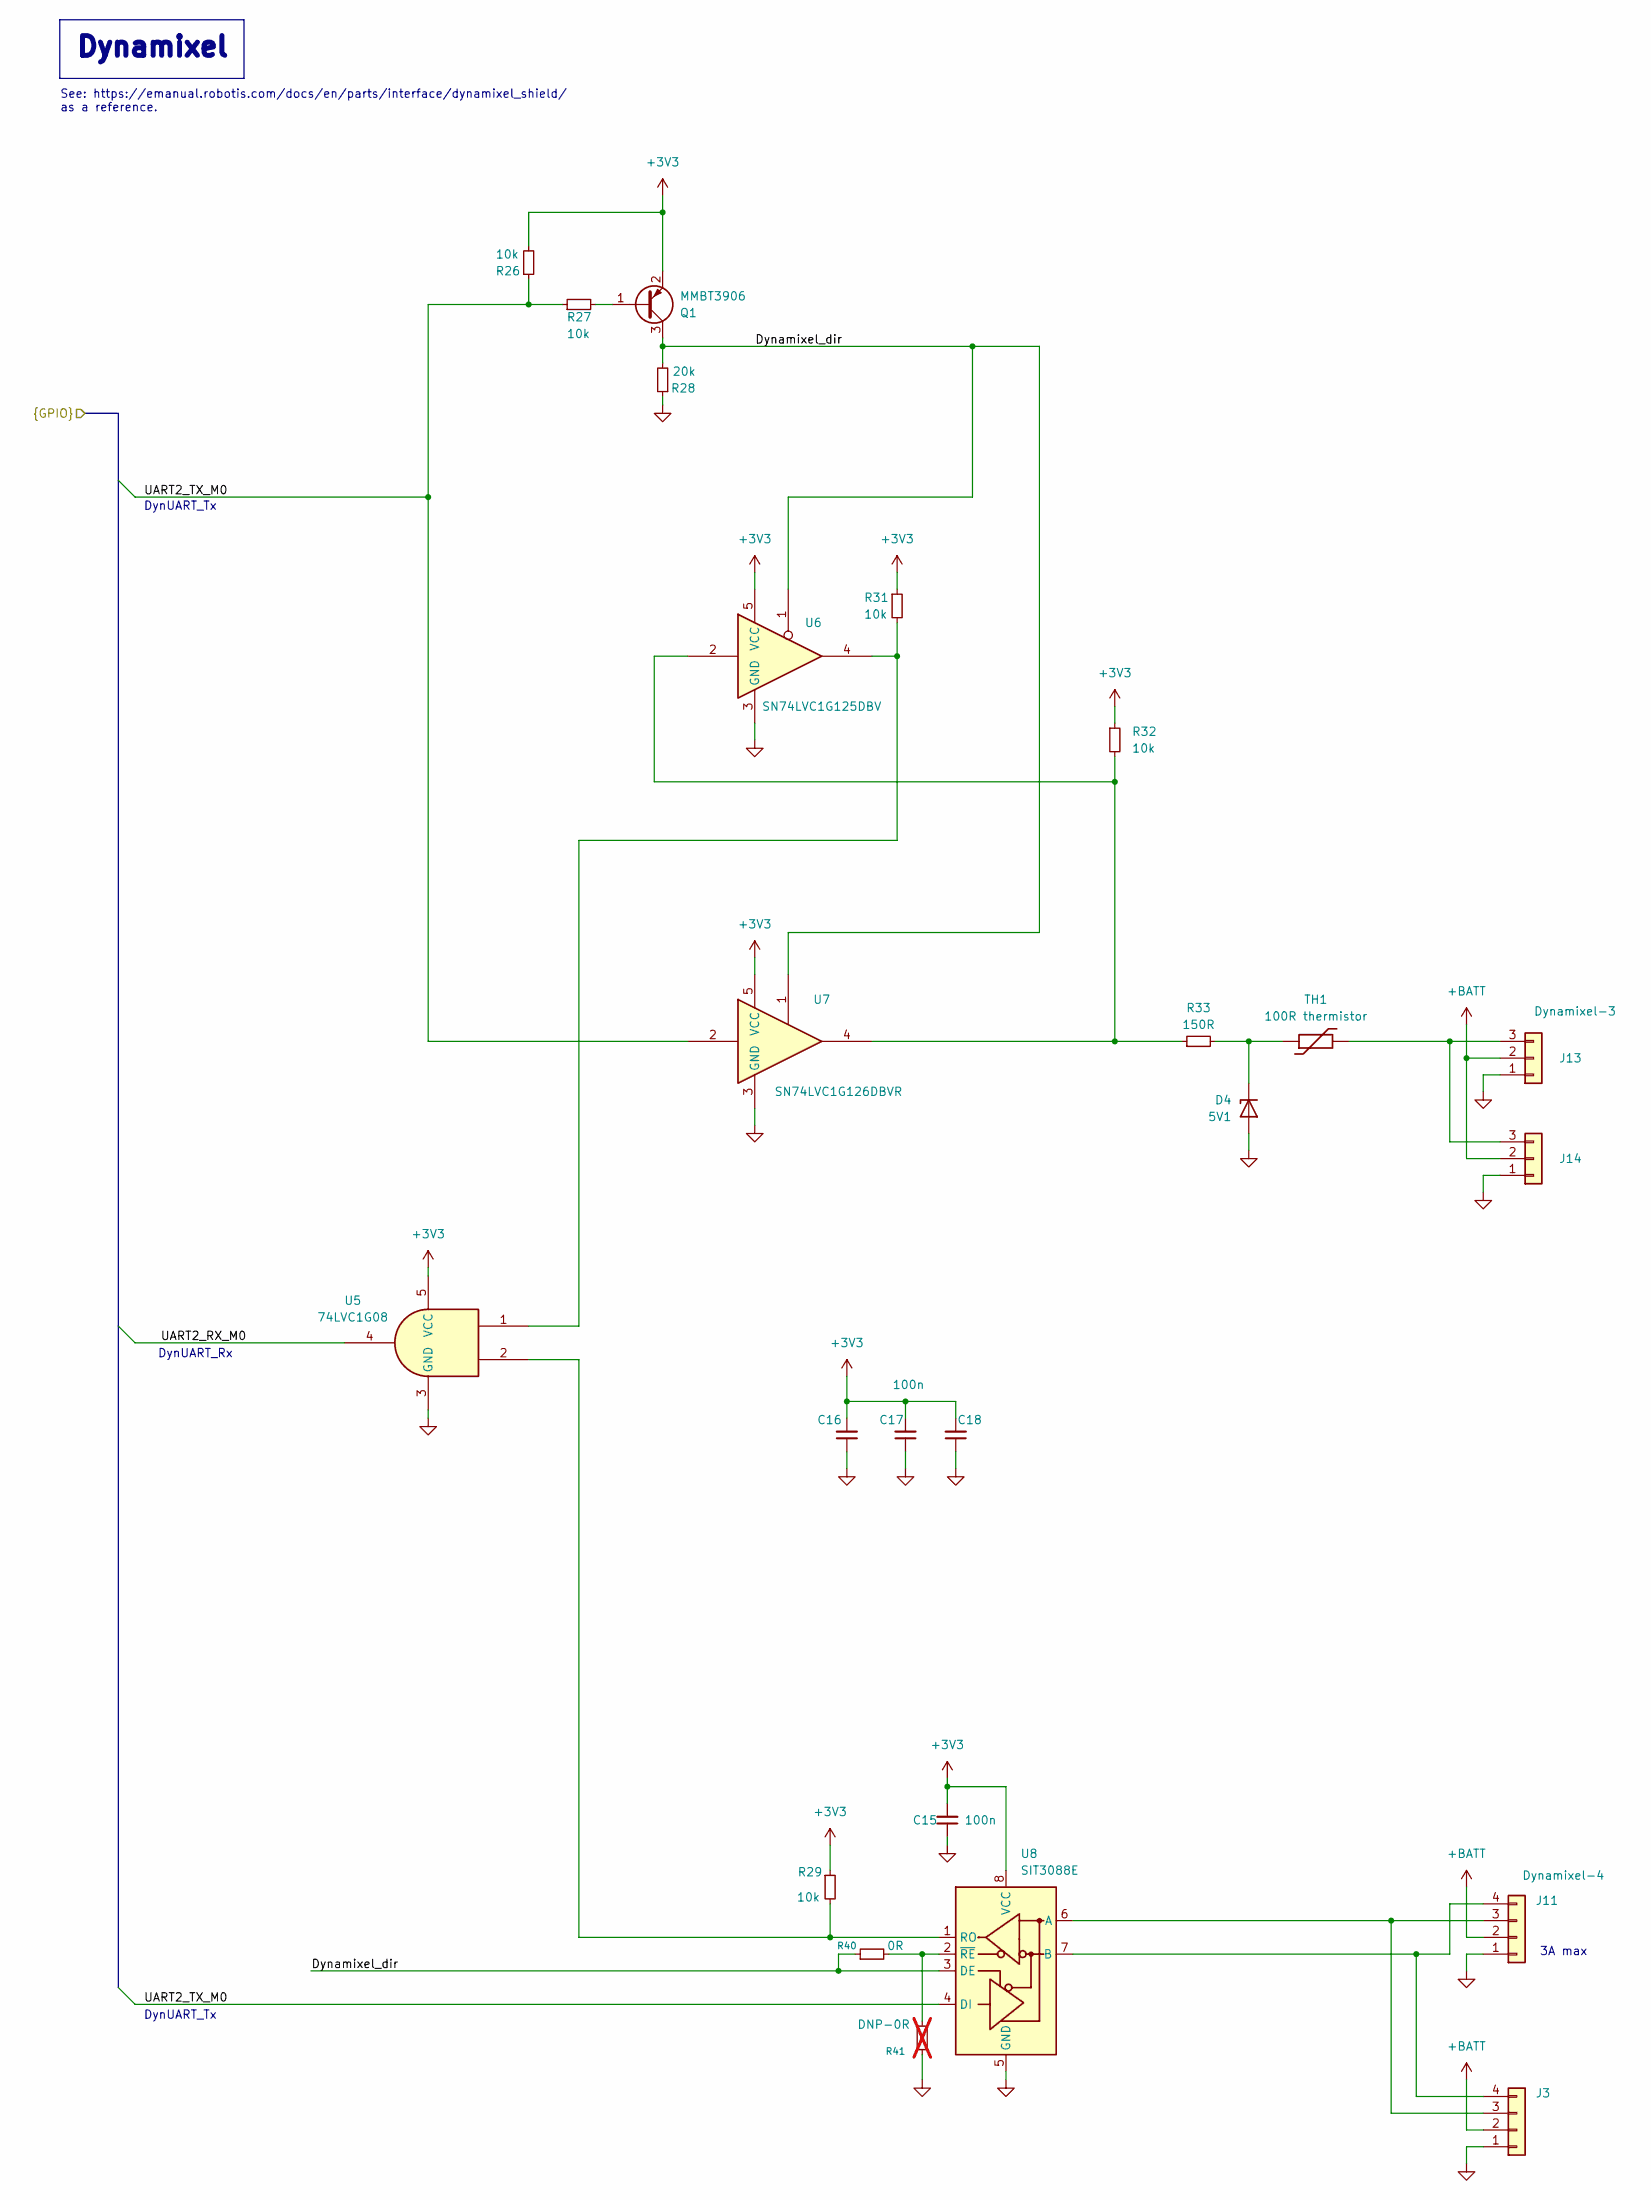
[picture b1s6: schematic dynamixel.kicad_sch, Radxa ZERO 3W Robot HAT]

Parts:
C15, C16, C17, C18: 100n; C_0402_1005Metric; LCSC Part C307331
D4: 5V1; D_SOD-323; LCSC Part C151348
J3, J11: Dynamixel-4; JST_EH_B4B-EH-A_1x04_P2.50mm_Vertical; LCSC Part C160258
J13, J14: Dynamixel-3; JST_EH_B3B-EH-A_1x03_P2.50mm_Vertical; LCSC Part C160259
Q1: MMBT3906; SOT-23; LCSC Part C727128
R26, R27, R29, R31, R32: 10k; R_0402_1005Metric; LCSC Part C25744
R28: 20k; R_0402_1005Metric; LCSC Part C25765
R33: 150R; R_0402_1005Metric; LCSC Part C138054
R40: 0R; R_0402_1005Metric; LCSC Part C17168
R41: DNP-0R; R_0402_1005Metric; not fitted
TH1: 100R thermistor; R_0603_1608Metric; LCSC Part C913703
U5: 74LVC1G08; SOT-23-5; LCSC Part C7666
U6: SN74LVC1G125DBV; SOT-23-5; LCSC Part C3040625
U7: SN74LVC1G126DBVR; SOT-23-5; LCSC Part C7834
U8: SIT3088E; MSOP-8-1EP_3x3mm_P0.65mm_EP1.5x1.8mm; LCSC Part C2922535

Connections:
+3V3: C15.2, C16.2, C17.2, C18.2, Q1.2 (E), R26.2, R29.1, R31.1, R32.1, U5.5 (VCC), U6.5 (VCC), U7.5 (VCC), U8.8 (VCC); also elsewhere on the board
+BATT: J3.2, J11.2, J13.2, J14.2; also elsewhere on the board
/Schematic/Audio/UART2_RX_M0: U5.4; also elsewhere on the board
/Schematic/Audio/UART2_TX_M0: R26.1, R27.1, U7.2, U8.4 (DI); also elsewhere on the board
/Schematic/Dynamixel/Dynamixel_dir: Q1.3 (C), R28.2, R40.1, U6.1, U7.1, U8.3 (DE)
GND: C15.1, C16.1, C17.1, C18.1, D4.2 (A), J3.1, J11.1, J13.1, J14.1, R28.1, R41.1, U5.3 (GND), U6.3 (GND), U7.3 (GND), U8.5 (GND); also elsewhere on the board
unnamed: D4.1 (K), R33.2, TH1.1
unnamed: J3.3, J11.3, U8.6 (A)
unnamed: J3.4, J11.4, U8.7 (B)
unnamed: J13.3, J14.3, TH1.2
unnamed: Q1.1 (B), R27.2
unnamed: R31.2, U5.1, U6.4
unnamed: R32.2, R33.1, U6.2, U7.4
unnamed: R29.2, U5.2, U8.1 (RO)
unnamed: R40.2, R41.2, U8.2 (~RE)

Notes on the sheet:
DynUART_Tx
DynUART_Rx
See: https://emanual.robotis.com/docs/en/parts/interface/dynamixel_shield/ as a reference.
3A max
Dynamixel
